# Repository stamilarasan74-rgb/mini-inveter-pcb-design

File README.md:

# mini-inveter-pcb-design
PCB Project Description

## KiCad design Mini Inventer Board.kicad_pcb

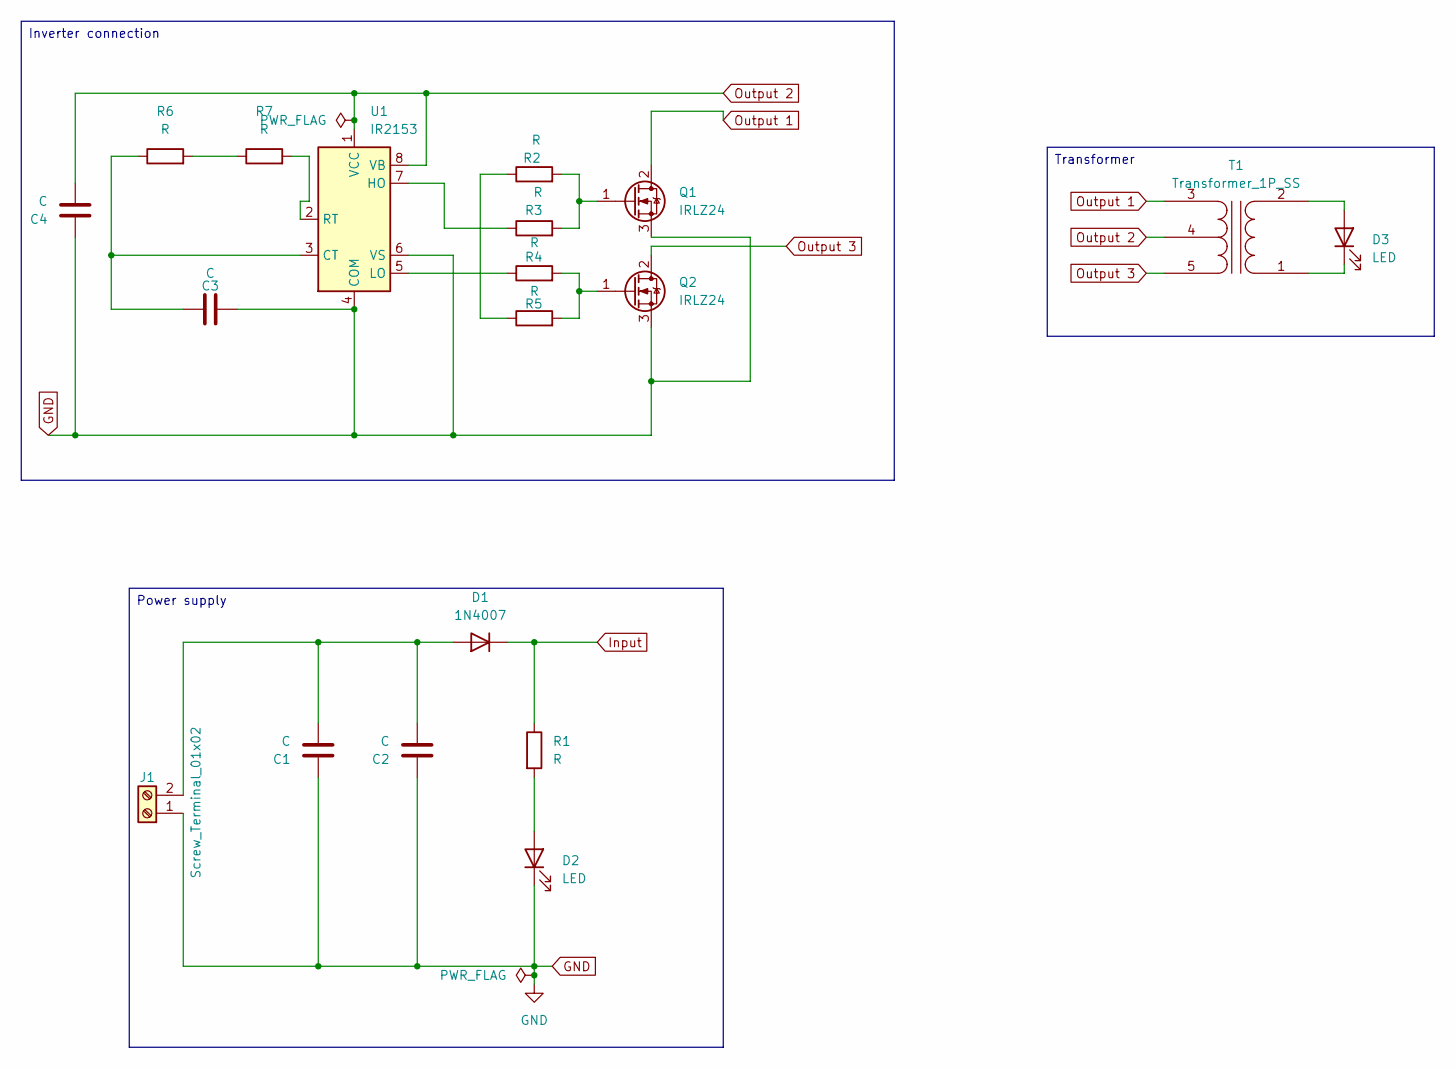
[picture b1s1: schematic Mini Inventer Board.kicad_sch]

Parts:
C1: C; CP_Radial_D4.0mm_P1.50mm
C2: C; CP_Radial_D5.0mm_P2.50mm
C3, C4: C; C_Disc_D4.3mm_W1.9mm_P5.00mm
D1: 1N4007; D_DO-41_SOD81_P7.62mm_Horizontal
D2: LED; LED_D3.0mm
D3: LED; TerminalBlock_MaiXu_MX126-5.0-02P_1x02_P5.00mm
J1: Screw_Terminal_01x02; TerminalBlock_MaiXu_MX126-5.0-02P_1x02_P5.00mm
Q1, Q2: IRLZ24; TO-220-3_Vertical
R1, R2, R3, R4, R5, R6, R7: R; R_Axial_DIN0204_L3.6mm_D1.6mm_P5.08mm_Horizontal
T1: Transformer_1P_SS; TerminalBlock_MaiXu_MX126-5.0-05P_1x05_P5.00mm
U1: IR2153; DIP-8_W7.62mm_SMDSocket_SmallPads

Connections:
GND: C1.1, C2.1, C3.1, C4.1, D2.1 (K), J1.1, Q1.3 (S), Q2.3 (S), U1.4 (COM), U1.6 (VS)
Input: D1.1 (K), R1.1
unnamed: C1.2, C2.2, D1.2 (A), J1.2
unnamed: D2.2 (A), R1.2
unnamed: D3.2 (A), T1.2 (AB)
unnamed: D3.1 (K), T1.1 (AA)
unnamed: Q1.1 (G), R2.2, R3.2
unnamed: Q2.1 (G), R4.2, R5.2
unnamed: R2.1, R5.1
unnamed: R6.2, R7.1
unnamed: C3.2, R6.1, U1.3 (CT)
unnamed: R3.1, U1.7 (HO)
unnamed: R4.1, U1.5 (LO)
unnamed: R7.2, U1.2 (RT)
Output 1: Q1.2 (D), T1.3 (SA)
Output 2: C4.2, T1.4 (SC), U1.1 (VCC), U1.8 (VB)
Output 3: Q2.2 (D), T1.5 (SB)

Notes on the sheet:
Power supply
Transformer
Inverter connection

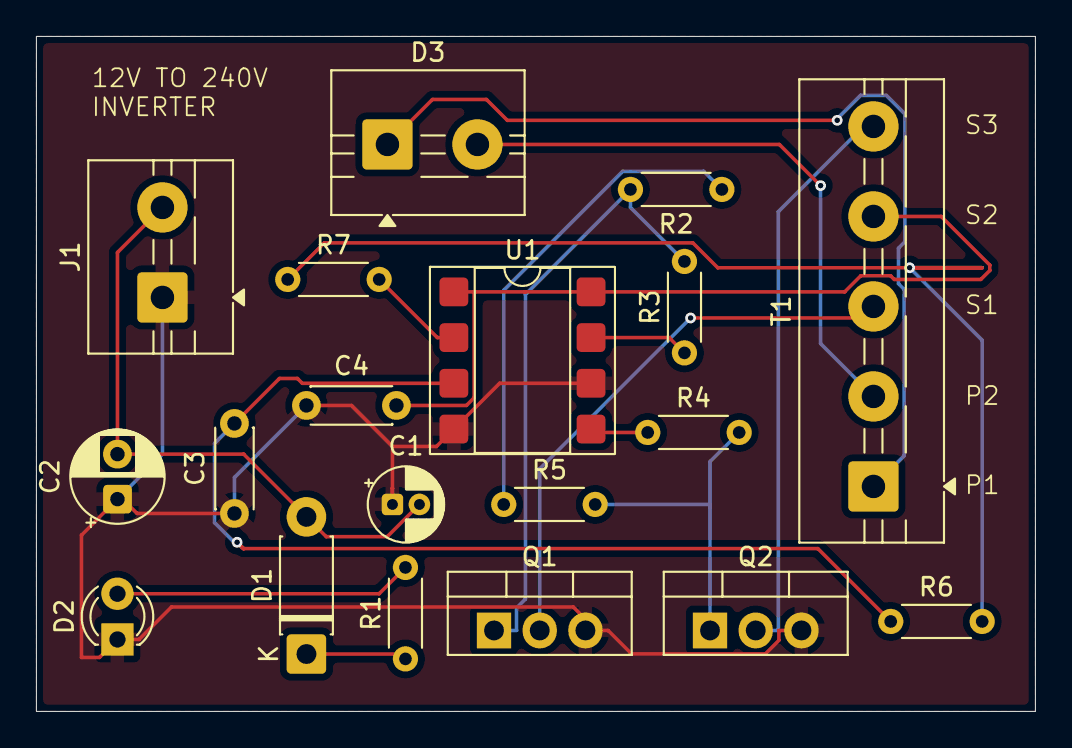
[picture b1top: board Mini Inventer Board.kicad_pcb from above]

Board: 2 copper layers, 55.5 x 37.5 mm, 19 parts (0 on the bottom side), 17 nets.
